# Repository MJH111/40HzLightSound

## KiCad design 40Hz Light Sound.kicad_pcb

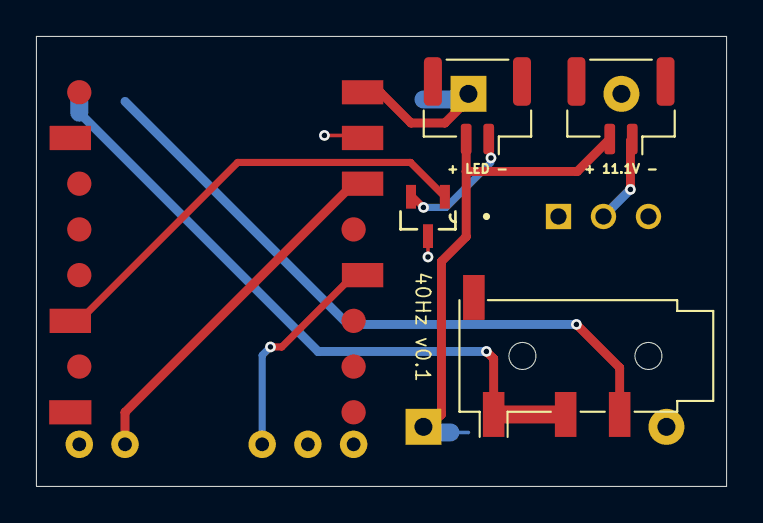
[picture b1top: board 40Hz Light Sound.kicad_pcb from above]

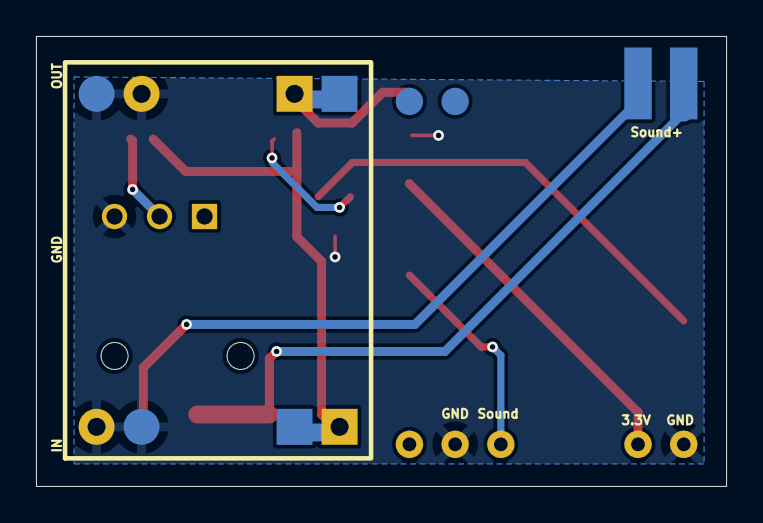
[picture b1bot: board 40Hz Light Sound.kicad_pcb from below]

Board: 2 copper layers, 38.3 x 25.0 mm, 8 parts (2 on the bottom side), 10 nets.

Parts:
+ 11.1V -: 11.1VDC; JST_GH_SM02B-GHS-TB_1x02-1MP_P1.25mm_Horizontal
+ LED -: LED_Conn; JST_GH_SM02B-GHS-TB_1x02-1MP_P1.25mm_Horizontal
J2: DC2DC; MP1584 FOOTPRINT
J3: Audio_Amp; pam8403
J5: AudioJack3_Ground; Jack_3.5mm_PJ320D_Horizontal
Q1: IRLML6344; SOT95P240X112-3N
SW1: SW_SPDT; SW_MINI-SPDT-SW
U1: ESP32-C3_SUPERMINI_TH; MODULE_ESP32-C3_SUPERMINI_TH

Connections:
3.3V: J3.4, U1.3.3 (3V3)
5VDC: J2.4, U1.5V
11.1V: + 11.1V -.2, + LED -.2, J2.2
11.1V_GND: + 11.1V -.1, SW1.2 (B)
GND: J2.1, J2.3, J3.2, J3.5, Q1.3, SW1.3 (C), U1.G (GND)
LED_GND: + LED -.1, Q1.2
LEDcontrol: Q1.1, U1.10 (GPIO10)
SoundControl: J3.3, U1.3 (GPIO3)
Sound_N: J3.7, J5.S
Sound_P: J3.6, J5.R, J5.T

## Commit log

2025-08-12 First Version
    initial version of 40 Hz cap design
2025-08-12 Submit v0.1 to order
